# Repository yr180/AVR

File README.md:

# AVR
Atmega 16/32 Boards and USBasp

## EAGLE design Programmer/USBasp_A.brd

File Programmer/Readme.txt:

This is the README file for USBasp.

USBasp is a USB in-circuit programmer for Atmel AVR controllers. It simply
consists of an ATMega88 or an ATMega8 and a couple of passive components.
The programmer uses a firmware-only USB driver, no special USB controller 
is needed.

Features:
- Works under multiple platforms. Linux, Mac OS X and Windows are tested.
- No special controllers or smd components are needed.
- Programming speed is up to 5kBytes/sec.
- SCK option to support targets with low clock speed (< 1,5MHz).
- Planned: serial interface to target (e.g. for debugging).

LIMITATIONS

Hardware:
This package includes a circuit diagram. This circuit can only be used for
programming 5V target systems. For other systems a level converter is needed.

Firmware:
The firmware dosn't support USB Suspend Mode. A bidirectional serial
interface to slave exists in hardware but the firmware doesn't support it yet.

USE PRECOMPILED VERSION

Firmware:
Flash "usbasp.atmega88.xxxx-xx-xx.hex" to the controller with a
working programmer (e.g. with avrdude, uisp, ...). 
Set jumper J2 to activate USBasp firmware update function.
You have to change the fuse bits for external crystal (see "make fuses").
# TARGET=atmega8    HFUSE=0xc9  LFUSE=0xef
# TARGET=atmega48   HFUSE=0xdd  LFUSE=0xff
# TARGET=atmega88   HFUSE=0xdd  LFUSE=0xff

Windows:
Start Windows and connect USBasp to the system. When Windows asks for a
driver, choose "bin/win-driver". On Win2k and WinXP systems, Windows will
warn that the driver is is not 'digitally signed'. Ignore this message and
continue with the installation.
Now you can run avrdude. Examples:
1. Enter terminal mode with an AT90S2313 connected to the programmer:
   avrdude -c usbasp -p at90s2313 -t
2. Write main.hex to the flash of an ATmega8:
   avrdude -c usbasp -p atmega8 -U flash:w:main.hex

Setting jumpers:
J1 Power target
   Supply target with 5V (USB voltage). Be careful with this option, the
   circuit isn't protected against short circuit!
J2 Jumper for firmware upgrade (not self-upgradable)
   Set this jumper for flashing the ATMega(4)8 of USBasp with another working
   programmer.
J3 SCK option
   If the target clock is lower than 1,5 MHz, you have to set this jumper.
   Then SCK is scaled down from 375 kHz to about 8 kHz.

MORE INFORMATION

For more information on USBasp and it's components please visit the
following URLs:

USBasp .......................... http://www.fischl.de/usbasp/

Firmware-only V-USB driver ...... http://www.obdev.at/products/vusb/
avrdude ......................... http://www.nongnu.org/avrdude/
libusb .......................... http://libusb.sourceforge.net/
libusb-win32 .................... http://libusb-win32.sourceforge.net/

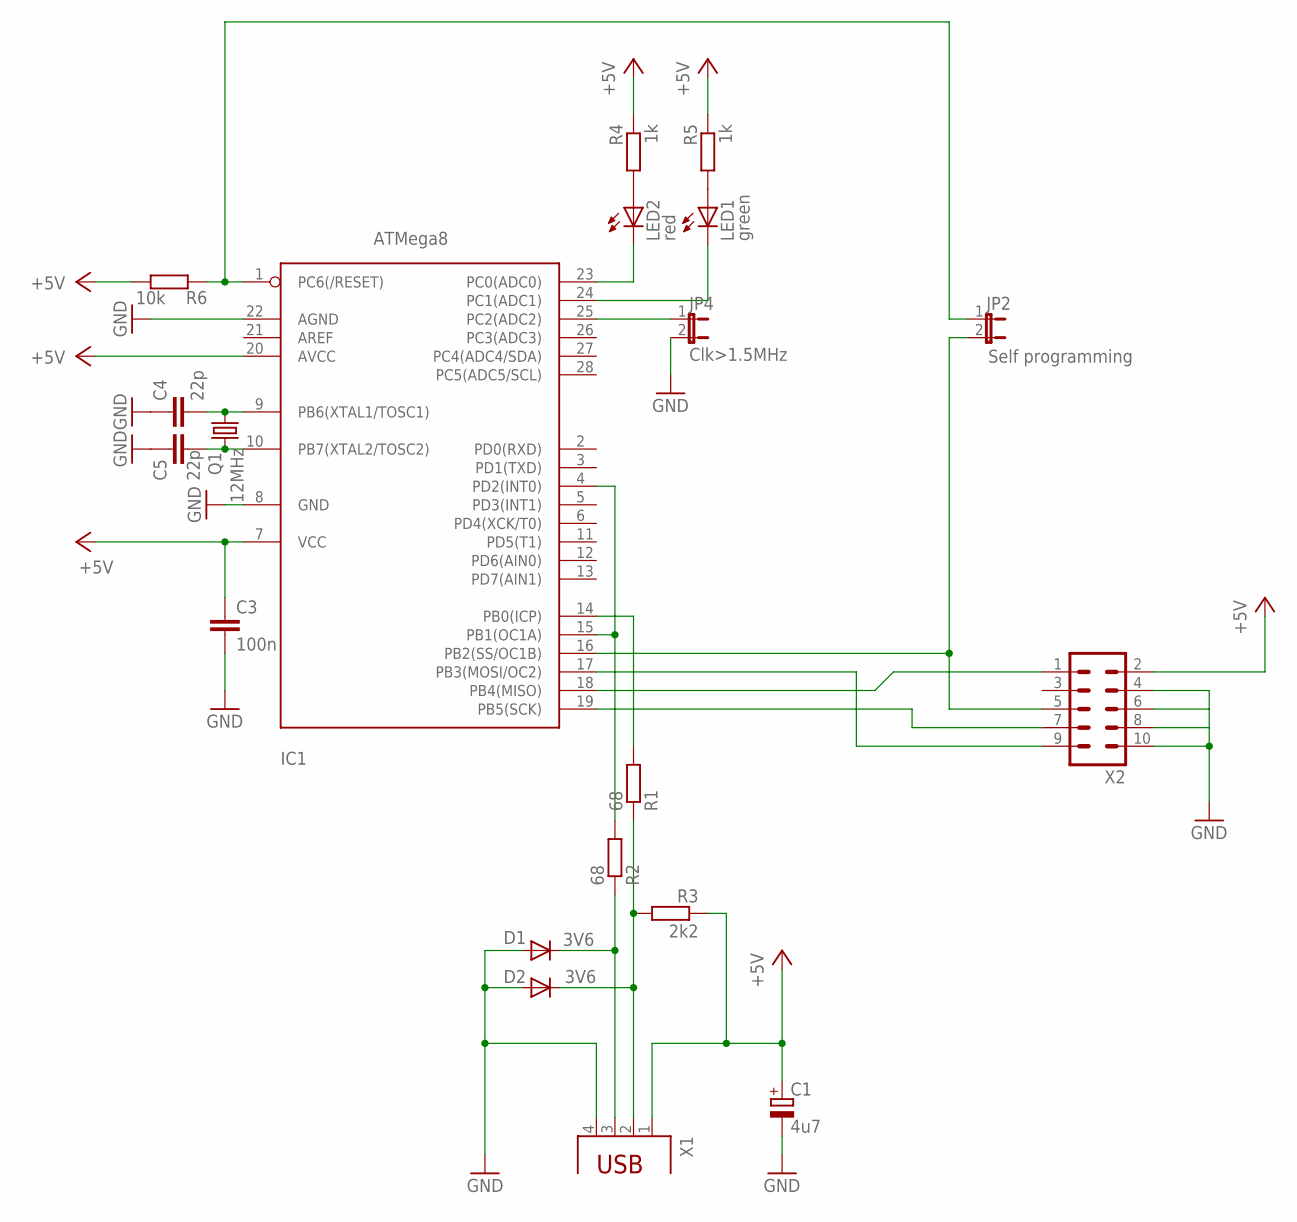
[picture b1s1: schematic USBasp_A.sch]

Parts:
C1: 4u7; E2,5-5
C3: 100n; C1206K
C4, C5: 22p; C1206K
D1, D2: 3V6; SOD80C
IC1: ATMega8; DIL28-3
JP2: Self programming; JP1
JP4: Clk>1.5MHz; JP1
LED1: green; LED3MM
LED2: red; LED3MM
Q1: 12MHz; HC49/S
R1, R2: 68; R1206W
R3: 2k2; R1206W
R4, R5: 1k; R1206W
R6: 10k; R1206W
X1: PN87520
X2: ML10

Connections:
+5V: C1.+, C3.1, IC1.7 (VCC), IC1.20 (AVCC), R3.1, R4.1, R5.1, R6.1, X1.1, X2.2
GND: C1.-, C3.2, C4.1, C5.1, D1.A, D2.A, IC1.8 (GND), IC1.22 (AGND), JP4.2, X1.4, X2.4, X2.6, X2.8, X2.10
unnamed: IC1.1 (PC6(/RESET)), JP2.1, R6.2
unnamed: IC1.16 (PB2(SS/OC1B)), JP2.2, X2.5
unnamed: IC1.17 (PB3(MOSI/OC2)), X2.9
unnamed: IC1.19 (PB5(SCK)), X2.7
unnamed: D2.C, R1.1, R3.2, X1.2
unnamed: IC1.4 (PD2(INT0)), IC1.15 (PB1(OC1A)), R2.2
unnamed: D1.C, R2.1, X1.3
unnamed: LED2.A, R4.2
unnamed: IC1.23 (PC0(ADC0)), LED2.K (C)
unnamed: IC1.24 (PC1(ADC1)), LED1.K (C)
unnamed: IC1.14 (PB0(ICP)), R1.2
unnamed: C4.2, IC1.9 (PB6(XTAL1/TOSC1)), Q1.2
unnamed: C5.2, IC1.10 (PB7(XTAL2/TOSC2)), Q1.1
unnamed: IC1.25 (PC2(ADC2)), JP4.1
unnamed: LED1.A, R5.2
unnamed: IC1.18 (PB4(MISO)), X2.1

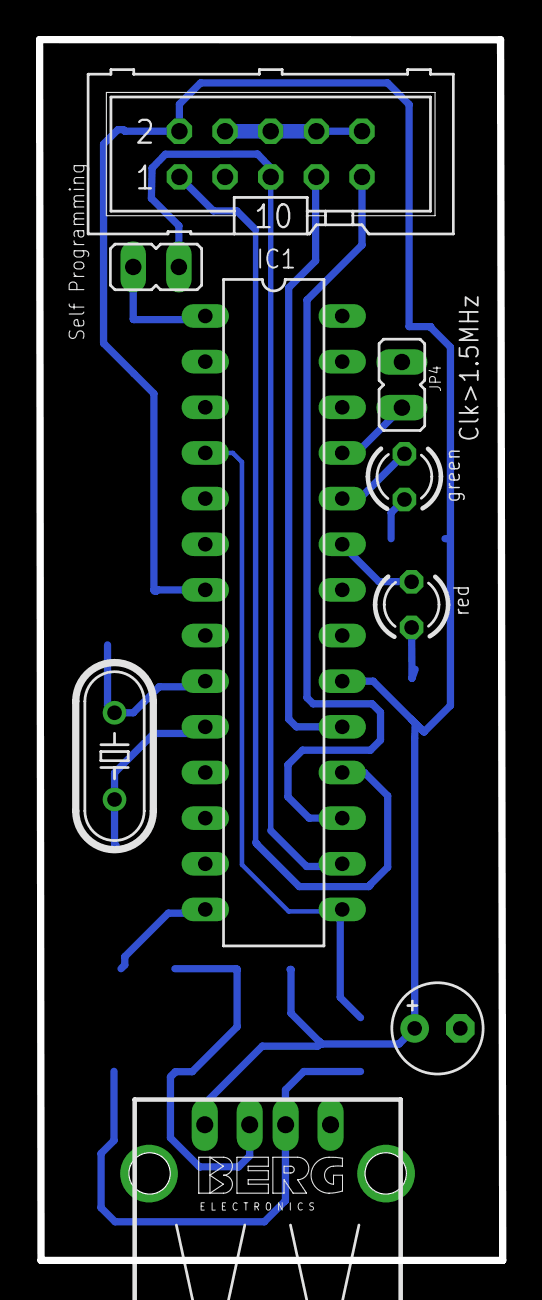
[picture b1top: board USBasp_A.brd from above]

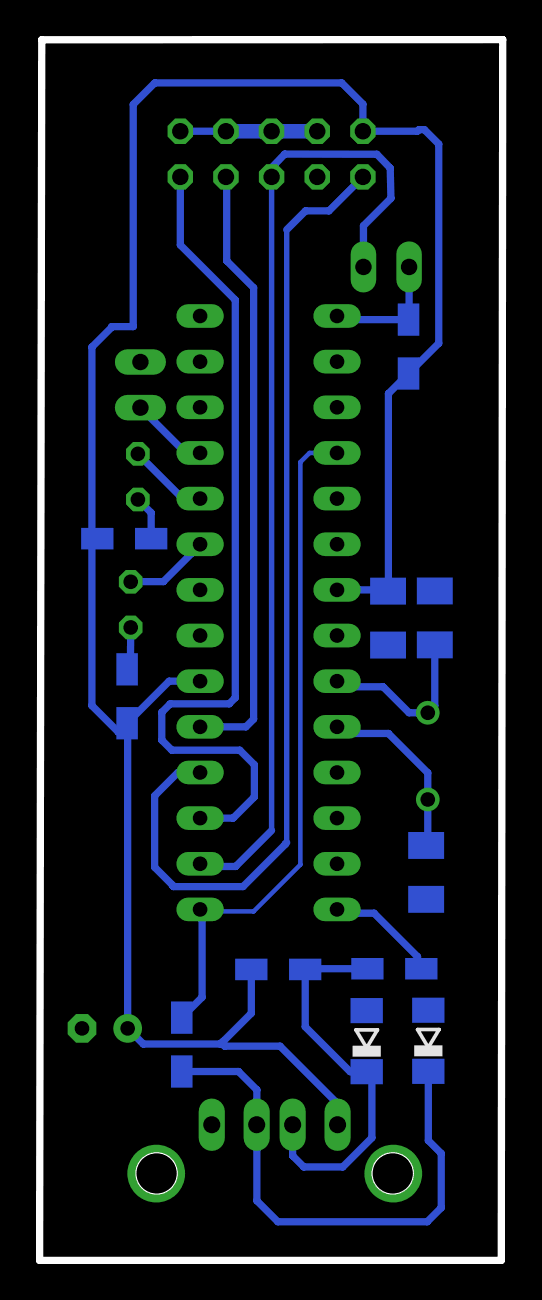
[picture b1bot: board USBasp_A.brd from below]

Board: 2 copper layers, 25.8 x 67.9 mm, 20 parts (11 on the bottom side), 18 nets.

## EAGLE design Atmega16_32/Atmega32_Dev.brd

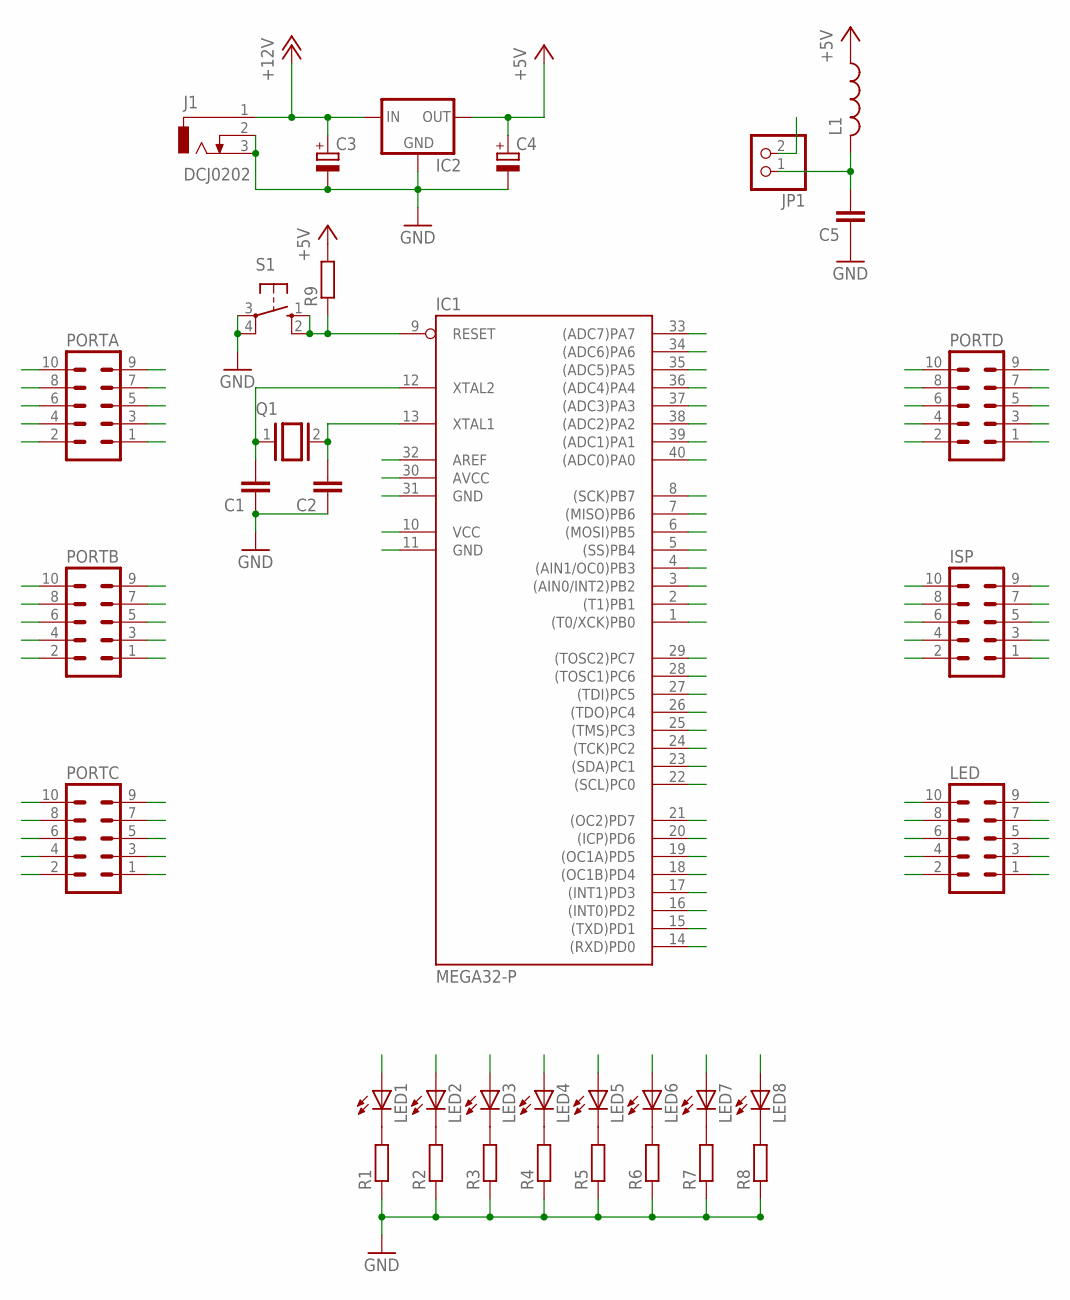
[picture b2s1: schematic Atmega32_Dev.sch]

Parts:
C1, C2, C5: CAP1206; 1206
C3, C4: CPOL-EUE5-6; E5-6
IC1: MEGA32-P; DIL40
IC2: 78XXL
ISP: ML10
J1: DCJ0202
JP1: PINHD-1X2; 1X02
L1: L-US0204/5; 0204/5
LED: ML10
LED1, LED2, LED3, LED4, LED5, LED6, LED7, LED8: LED3MM
PORTA: ML10
PORTB: ML10
PORTC: ML10
PORTD: ML10
Q1: XTAL/S; QS
R1, R2, R3, R4, R5, R6, R7, R8: R-EU_M1206; M1206
R9: R-EU_0204/7; 0204/7
S1: 10-XX; B3F-10XX

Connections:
+5V: C4.+, IC1.10 (VCC), IC2.OUT, ISP.2, L1.1, LED.9, PORTA.9, PORTB.9, PORTC.9, PORTD.9, R9.2
+12V: C3.+, IC2.IN, J1.1
AREF: IC1.32 (AREF), JP1.2
AVCC: C5.2, IC1.30 (AVCC), JP1.1, L1.2
GND: C1.1, C2.1, C3.-, C4.-, C5.1, IC1.11 (GND), IC1.31 (GND), IC2.GND, ISP.4, ISP.6, ISP.8, ISP.10, J1.2, J1.3, LED.10, PORTA.10, PORTB.10, PORTC.10, PORTD.10, R1.1, R2.1, R3.1, R4.1, R5.1, R6.1, R7.1, R8.1, S1.3, S1.4 (P1)
L0: LED.1, LED1.A
L1: LED.2, LED2.A
L2: LED.3, LED3.A
L3: LED.4, LED4.A
L4: LED.5, LED5.A
L5: LED.6, LED6.A
L6: LED.7, LED7.A
L7: LED.8, LED8.A
unnamed: LED1.K (C), R1.2
unnamed: LED2.K (C), R2.2
unnamed: LED3.K (C), R3.2
unnamed: LED4.K (C), R4.2
unnamed: LED5.K (C), R5.2
unnamed: LED6.K (C), R6.2
unnamed: LED7.K (C), R7.2
unnamed: LED8.K (C), R8.2
unnamed: C1.2, IC1.12 (XTAL2), Q1.1
unnamed: C2.2, IC1.13 (XTAL1), Q1.2
PA0: IC1.40 ((ADC0)PA0), PORTA.1
PA1: IC1.39 ((ADC1)PA1), PORTA.2
PA2: IC1.38 ((ADC2)PA2), PORTA.3
PA3: IC1.37 ((ADC3)PA3), PORTA.4
PA4: IC1.36 ((ADC4)PA4), PORTA.5
PA5: IC1.35 ((ADC5)PA5), PORTA.6
PA6: IC1.34 ((ADC6)PA6), PORTA.7
PA7: IC1.33 ((ADC7)PA7), PORTA.8
PB0: IC1.1 ((T0/XCK)PB0), PORTB.1
PB1: IC1.2 ((T1)PB1), PORTB.2
PB2: IC1.3 ((AIN0/INT2)PB2), PORTB.3
PB3: IC1.4 ((AIN1/OC0)PB3), PORTB.4
PB4: IC1.5 ((SS)PB4), PORTB.5
PB5: IC1.6 ((MOSI)PB5), ISP.9, PORTB.6
PB6: IC1.7 ((MISO)PB6), ISP.1, PORTB.7
PB7: IC1.8 ((SCK)PB7), ISP.7, PORTB.8
PC0: IC1.22 ((SCL)PC0), PORTC.1
PC1: IC1.23 ((SDA)PC1), PORTC.2
PC2: IC1.24 ((TCK)PC2), PORTC.3
PC3: IC1.25 ((TMS)PC3), PORTC.4
PC4: IC1.26 ((TDO)PC4), PORTC.5
PC5: IC1.27 ((TDI)PC5), PORTC.6
PC6: IC1.28 ((TOSC1)PC6), PORTC.7
PC7: IC1.29 ((TOSC2)PC7), PORTC.8
PD0: IC1.14 ((RXD)PD0), PORTD.1
PD1: IC1.15 ((TXD)PD1), PORTD.2
PD2: IC1.16 ((INT0)PD2), PORTD.3
PD3: IC1.17 ((INT1)PD3), PORTD.4
PD4: IC1.18 ((OC1B)PD4), PORTD.5
PD5: IC1.19 ((OC1A)PD5), PORTD.6
PD6: IC1.20 ((ICP)PD6), PORTD.7
PD7: IC1.21 ((OC2)PD7), PORTD.8
RESET: IC1.9 (RESET), ISP.5, R9.1, S1.1 (S), S1.2 (S1)

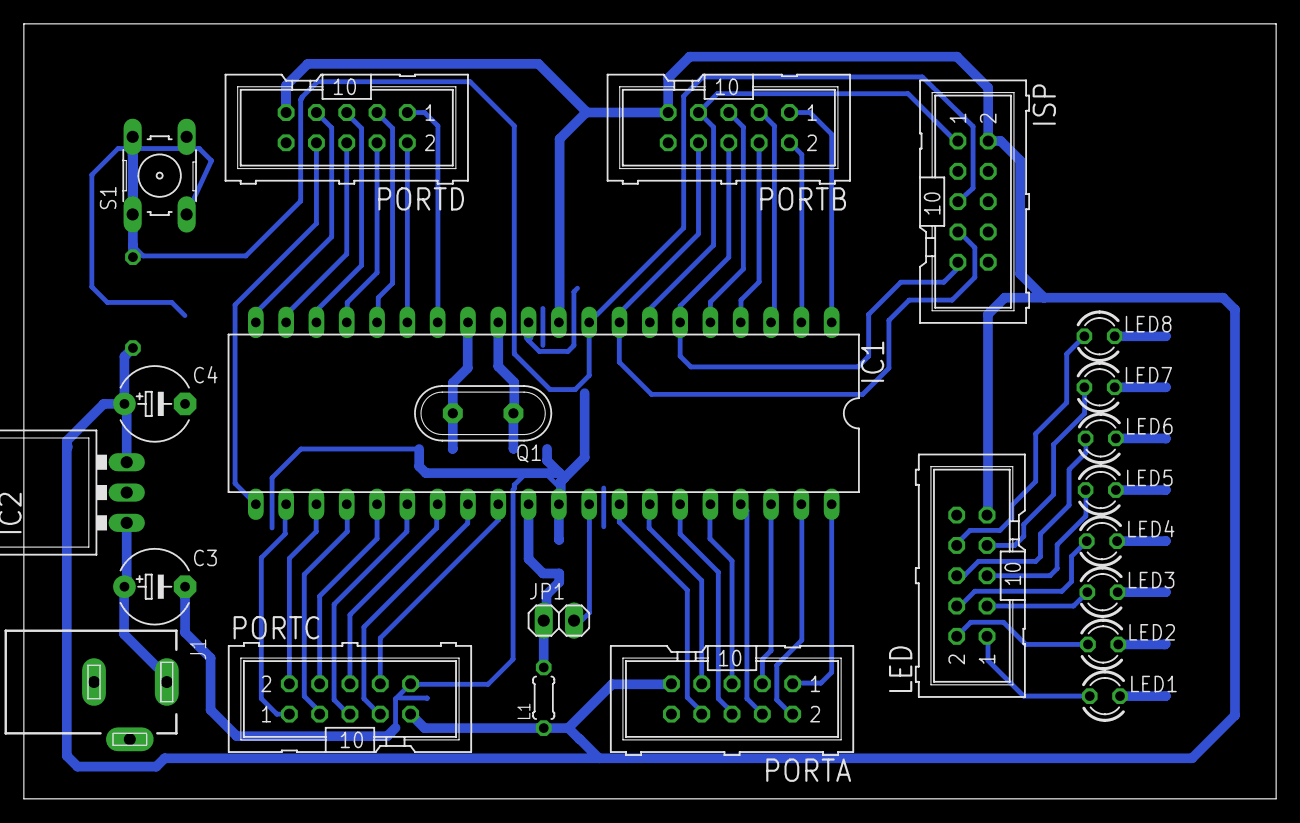
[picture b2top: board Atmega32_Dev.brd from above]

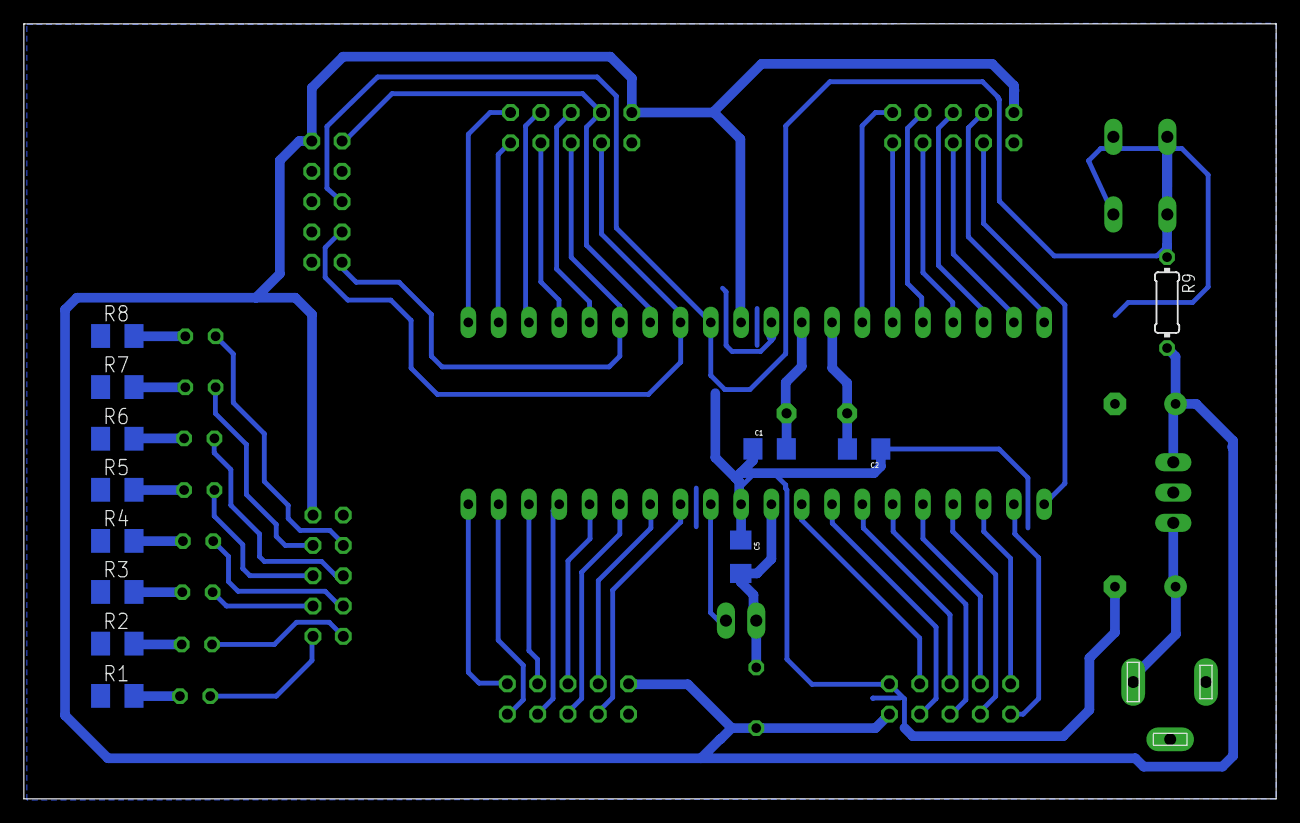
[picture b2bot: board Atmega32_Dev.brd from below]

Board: 2 copper layers, 105.0 x 65.0 mm, 35 parts (12 on the bottom side), 56 nets.

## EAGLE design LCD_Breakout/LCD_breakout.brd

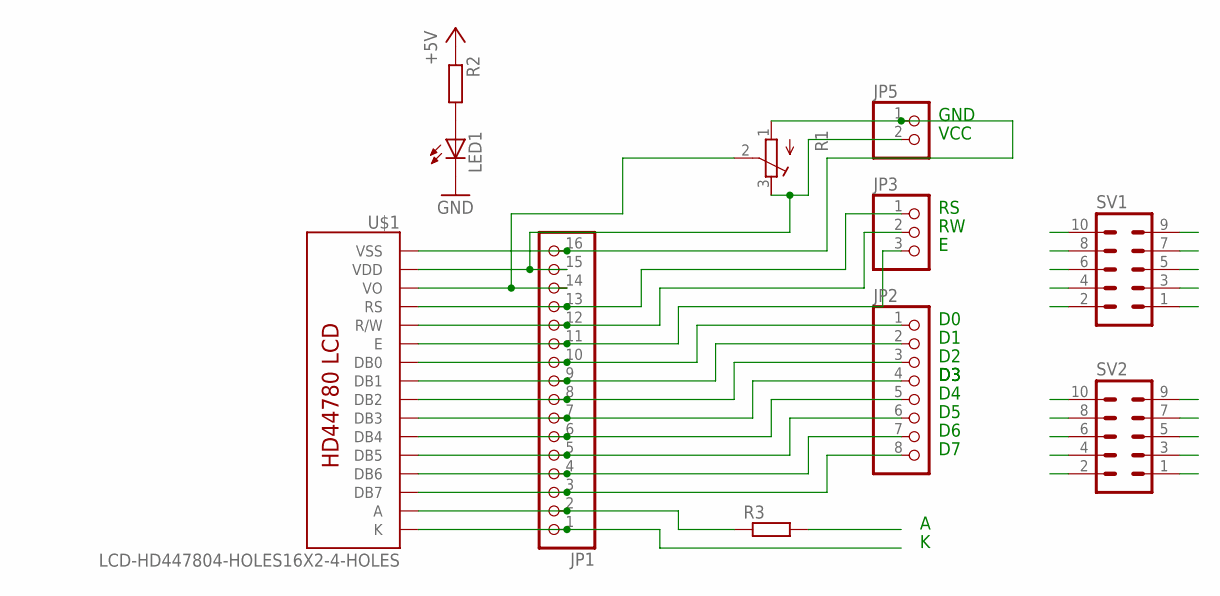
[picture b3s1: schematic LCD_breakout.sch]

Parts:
JP1: PINHD-1X16; 1X16
JP2: PINHD-1X8; 1X08
JP3: PINHD-1X3; 1X03
JP5: PINHD-1X2; 1X02
LED1: LED3MM
R1: R-TRIMM3339P; RTRIM3339P
R2, R3: R-EU_0204/5; 0204/5
SV1, SV2: ML10
U$1: LCD-HD447804-HOLES16X2-4-HOLES; LCD-16X2-4HOLES

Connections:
+5V: JP1.15, JP5.2, R1.3 (A), R2.1, R3.2, SV1.9, SV2.9, U$1.2 (VDD)
D0: JP1.10, JP2.1, SV2.1, U$1.7 (DB0)
D1: JP1.9, JP2.2, SV2.2, U$1.8 (DB1)
D2: JP1.8, JP2.3, SV2.3, U$1.9 (DB2)
D3: JP1.7, JP2.4, SV2.4, U$1.10 (DB3)
D4: JP1.6, JP2.5, SV2.5, U$1.11 (DB4)
D5: JP1.5, JP2.6, SV2.6, U$1.12 (DB5)
D6: JP1.4, JP2.7, SV2.7, U$1.13 (DB6)
D7: JP1.3, JP2.8, SV2.8, U$1.14 (DB7)
EN: JP1.11, JP3.3, SV1.3, U$1.6 (E)
GND: JP1.1, JP1.16, JP5.1, LED1.K (C), R1.1 (E), SV1.10, SV2.10, U$1.1 (VSS), U$1.16 (K)
unnamed: JP1.14, R1.2 (S), U$1.3 (VO)
unnamed: LED1.A, R2.2
unnamed: JP1.2, R3.1, U$1.15 (A)
RS: JP1.13, JP3.1, SV1.1, U$1.4 (RS)
RW: JP1.12, JP3.2, SV1.2, U$1.5 (R/W)

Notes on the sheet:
VCC
GND

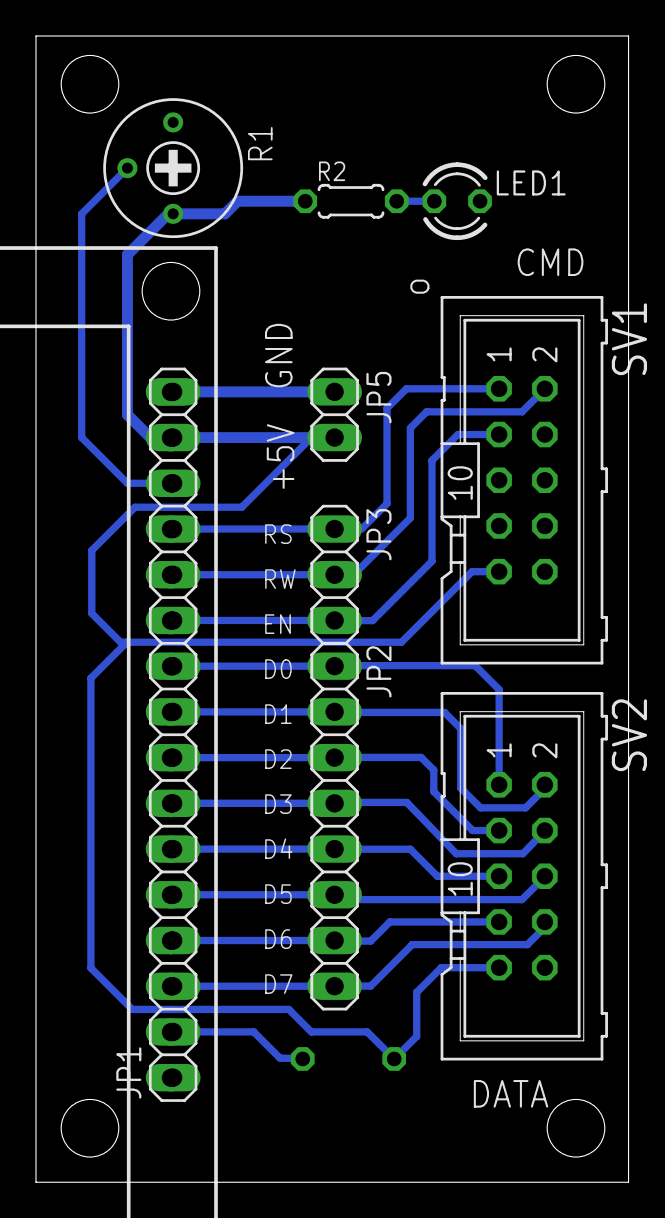
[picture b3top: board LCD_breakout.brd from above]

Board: 2 copper layers, 32.9 x 63.7 mm, 11 parts (1 on the bottom side), 16 nets.

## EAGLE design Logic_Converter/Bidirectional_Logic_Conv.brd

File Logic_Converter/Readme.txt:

Description of the level shift operation. [Source - Philips AN97055]
For the level shift operation, following three states have to be considered:

• State 1:
	 No device is pulling down the bus line and the bus line of the “Lower voltage” section is pulled up
by its pull-up resistors Rp to 3.3 V. The gate and the source of the MOS-FET are both at 3.3 V, so its VGS
is below the threshold voltage and the MOS-FET is not conducting. This allows that the bus line at the
“Higher voltage” section is pulled up by its pull-up resistor Rp to 5V. So the bus lines of both sections are
HIGH, but at a different voltage level.

• State 2:
	 A 3.3 V device pulls down the bus line to a LOW level. The source of the MOS-FET becomes
also LOW, while the gate stay at 3.3 V. The VGS rises above the threshold and the MOS-FET becomes
conducting. Now the bus line of the “Higher voltage” section is also pulled down to a LOW level by the 3.3
V device via the conducting MOS-FET. So the bus lines of both sections become LOW at the same
voltage level.

• State 3:
	 A 5 V device pulls down the bus line to a LOW level. Via the drain-substrate diode of the MOSFET
the “Lower voltage” section is in first instance pulled down until VGS passes the threshold and the
MOS-FET becomes conducting. Now the bus line of the “Lower voltage” section is further pulled down to
a LOW level by the 5 V device via the conducting MOS-FET. So the bus lines of both sections become
LOW at the same voltage level.

The three states show that the logic levels are transferred in both directions of the bus system, independent of
the driving section.
Other supply voltages than 3.3V for VDD1 and 5V for VDD2 can be applied. In normal operation VDD2 must be equal 
to or higher than VDD1.

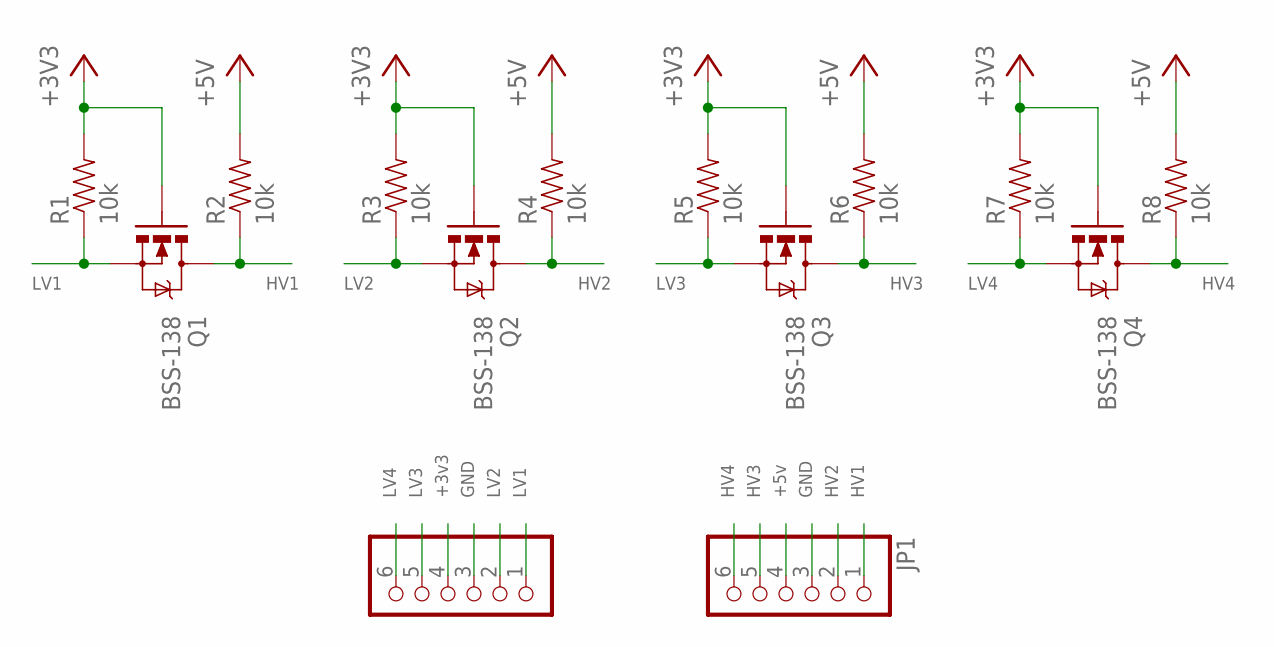
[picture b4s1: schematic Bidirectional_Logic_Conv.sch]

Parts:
JP1: PINHD-1X6; 1X06
Q1, Q2, Q3, Q4: BSS-138; SOT23-3
R1, R2, R3, R4, R5, R6, R7, R8: 10k; 1206
 : PINHD-1X6; 1X06

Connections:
+3V3: Q1.1 (G), Q2.1 (G), Q3.1 (G), Q4.1 (G), R1.2, R3.2, R5.2, R7.2, .4
+5V: JP1.4, R2.2, R4.2, R6.2, R8.2
GND: JP1.3, .3
HV1: JP1.1, Q1.3 (D), R2.1
HV2: JP1.2, Q2.3 (D), R4.1
HV3: JP1.5, Q3.3 (D), R6.1
HV4: JP1.6, Q4.3 (D), R8.1
LV1: Q1.2 (S), R1.1, .1
LV2: Q2.2 (S), R3.1, .2
LV3: Q3.2 (S), R5.1, .5
LV4: Q4.2 (S), R7.1, .6

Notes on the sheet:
LV1
LV2
LV3
LV4
+3v3
GND
+5v
HV1
HV2
HV3
HV4

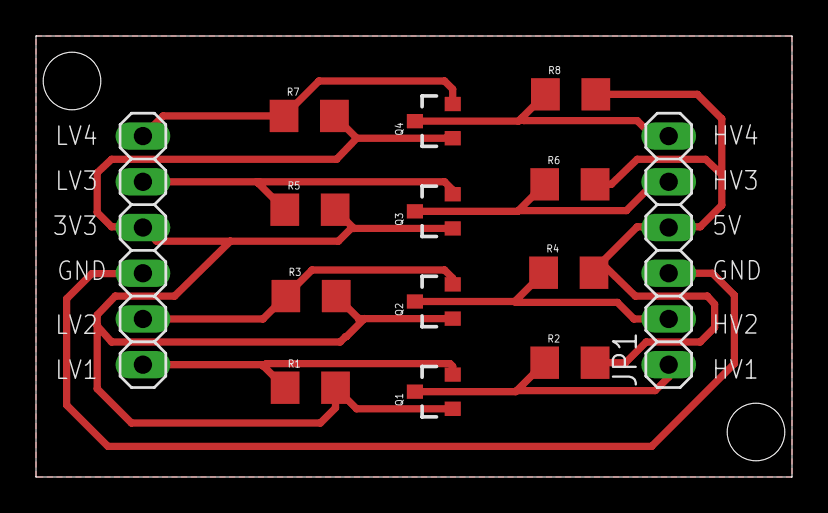
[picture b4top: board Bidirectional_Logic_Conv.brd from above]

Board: 2 copper layers, 42.0 x 24.5 mm, 14 parts (0 on the bottom side), 11 nets.

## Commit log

2017-04-27 Create abc
2017-04-27 Rename USBasp.brd to USBasp_B.brd
2017-04-27 Rename USBasp.sch to USBasp_B.sch
